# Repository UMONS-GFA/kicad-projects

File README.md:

# kicad-projects (NOT USED ANYMORE !)

## Configuring libraries in a project

Open your .sch file -> Preferences -> Component libraries  

Add component library files and choose your .lib files from the project_libs directory.  

## Configuring footprints in a project

* In project window, click new directory, rename it project_libs
* Add .lib files in this folder
* create project\_footprint.pretty sub-directory in project_libs
* Add kicad_mods in this sub-directory

Now in footprint editor, preferences -> footprint libraries manager-> project specific libraries click on on "Append Library"  

Example:  

Nickname: project  
Library path: ${KPRJMOD}/project\_libs/project\_footprints.pretty

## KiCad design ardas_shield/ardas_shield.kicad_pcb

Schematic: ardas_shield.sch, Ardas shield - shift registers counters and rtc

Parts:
BT1: Battery; BATTERY_KEYSTONE_12mm
D1, D2, D3: LED; LED-0805
IC1: DS1307; SOIC-8-N
JP1: Jumper_NO_Small; small_no_jumper
P1: CONN_10; Pin_Header_Straight_1x10
P2, P3: CONN_8; Pin_Header_Straight_1x08
P4: CONN_ICSP; Socket_Strip_Straight_2x03
P5: CONN_6; Pin_Header_Straight_1x06
P6: TTL_COMM; Pin_Header_Angled_1x03
P7, P8, P9, P10: CONN_01X03; Pin_Header_Angled_1x03
R1: 10k; R_0805
R2, R3: 150 Ohm; R_0805
R4: 160 Ohm; R_0805
RP1: R_4x4.7k; R_Array_Convex_4x0603
RP2, RP3, RP4, RP5: R_4x10k; R_Array_Convex_4x0603
U1: 74HC595; SOIC-16_7.5x10.3mm_Pitch1.27mm
U2, U4: 74HC165; SOIC-16_3.9x9.9mm_Pitch1.27mm
U3, U6: SN74LV8154; TSSOP-20_4.4x6.5mm_Pitch0.65mm
X1: CRYSTAL; XTAL_ABRACON_ABS07

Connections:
+5V: D1.2, D2.2, D3.2, IC1.8 (VCC), P2.5, P4.2, P7.1, P8.1, P9.1, P10.1, RP1.1, RP1.5 (R4), RP1.6 (R3), RP1.7 (R2), RP2.1, RP2.2, RP2.3, RP2.4, RP4.3, RP4.5 (R4), RP5.1, RP5.2, RP5.3, RP5.4, U1.16 (VCC), U2.16 (VCC), U3.20 (VCC), U4.16 (VCC), U6.20 (VCC)
A04: IC1.5 (SDA), P1.9, RP1.4
A05: IC1.6 (SCL), P1.10, RP1.3
CH1: P10.3, U3.1 (CLKA)
CH2: P9.3, U3.2 (CLKB)
CH3: P8.3, U6.1 (CLKA)
CH4: P7.3, U6.2 (CLKB)
D00: P3.1, P6.2
D01: P3.2, P6.1
D02: IC1.7 (SQW), P3.3, RP1.2
D03: P3.4, U1.11 (SRCLK)
D05: P3.6, U1.14 (SER)
D06: P3.7, U1.12 (RCLK)
D07: P3.8, U2.9 (Q7)
D08: P1.1, U2.1 (PL), U4.1 (PL)
D09: P1.2, RP4.1, RP4.2, U2.15 (CE), U4.15 (CE)
D14: P5.1, U3.7 (RCLK), U6.7 (RCLK)
D15: P5.2, U2.2 (CP), U4.2 (CP)
D16: P5.3, R3.2
D17: P5.4, R2.2
GND: BT1.2, IC1.4 (GND), JP1.1, P1.7, P2.6, P2.7, P4.6, P6.3, P7.2, P8.2, P9.2, P10.2, R1.1, R4.2, RP3.5 (R4), RP3.6 (R3), RP3.7 (R2), RP3.8 (R1), RP4.7 (R2), RP4.8 (R1), U1.8 (GND), U2.8 (GND), U3.10 (GND), U4.8 (GND), U6.10 (GND)
unnamed: BT1.1, IC1.3 (VBAT), JP1.2
unnamed: D1.1, R2.1
unnamed: D2.1, R3.1
unnamed: D3.1, R4.1
unnamed: IC1.1 (X1), X1.1
unnamed: IC1.2 (X2), X1.2
unnamed: R1.2, U1.13 (G)
unnamed: RP1.8 (R1), U1.10 (SRCLR)
unnamed: RP2.5 (R4), U1.15 (QA), U3.6 (GBU)
unnamed: RP2.6 (R3), U1.1 (QB), U3.5 (GBL)
unnamed: RP2.7 (R2), U1.2 (QC), U3.4 (GAU)
unnamed: RP2.8 (R1), U1.3 (QD), U3.3 (GAL)
unnamed: RP3.1, U3.8 (RCOA)
unnamed: RP3.2, U3.9 (CLKBEN)
unnamed: RP3.3, U6.8 (RCOA)
unnamed: RP3.4, U6.9 (CLKBEN)
unnamed: RP4.4, U6.11 (CCLR)
unnamed: RP4.6 (R3), U3.11 (CCLR)
unnamed: RP5.5 (R4), U1.4 (QE), U6.6 (GBU)
unnamed: RP5.6 (R3), U1.5 (QF), U6.5 (GBL)
unnamed: RP5.7 (R2), U1.6 (QG), U6.4 (GAU)
unnamed: RP5.8 (R1), U1.7 (QH), U6.3 (GAL)
unnamed: U2.3 (D4), U3.15 (Y4)
unnamed: U2.4 (D5), U3.14 (Y5)
unnamed: U2.5 (D6), U3.13 (Y6)
unnamed: U2.6 (D7), U3.12 (Y7)
unnamed: U2.10 (DS), U4.9 (Q7)
unnamed: U2.11 (D0), U3.19 (Y0)
unnamed: U2.12 (D1), U3.18 (Y1)
unnamed: U2.13 (D2), U3.17 (Y2)
unnamed: U2.14 (D3), U3.16 (Y3)
unnamed: U4.3 (D4), U6.15 (Y4)
unnamed: U4.4 (D5), U6.14 (Y5)
unnamed: U4.5 (D6), U6.13 (Y6)
unnamed: U4.6 (D7), U6.12 (Y7)
unnamed: U4.11 (D0), U6.19 (Y0)
unnamed: U4.12 (D1), U6.18 (Y1)
unnamed: U4.13 (D2), U6.17 (Y2)
unnamed: U4.14 (D3), U6.16 (Y3)

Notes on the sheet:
Arduino Uno R3 connectors
SHOULDN'T WE SET PIN 10 TO GND OR VCC?

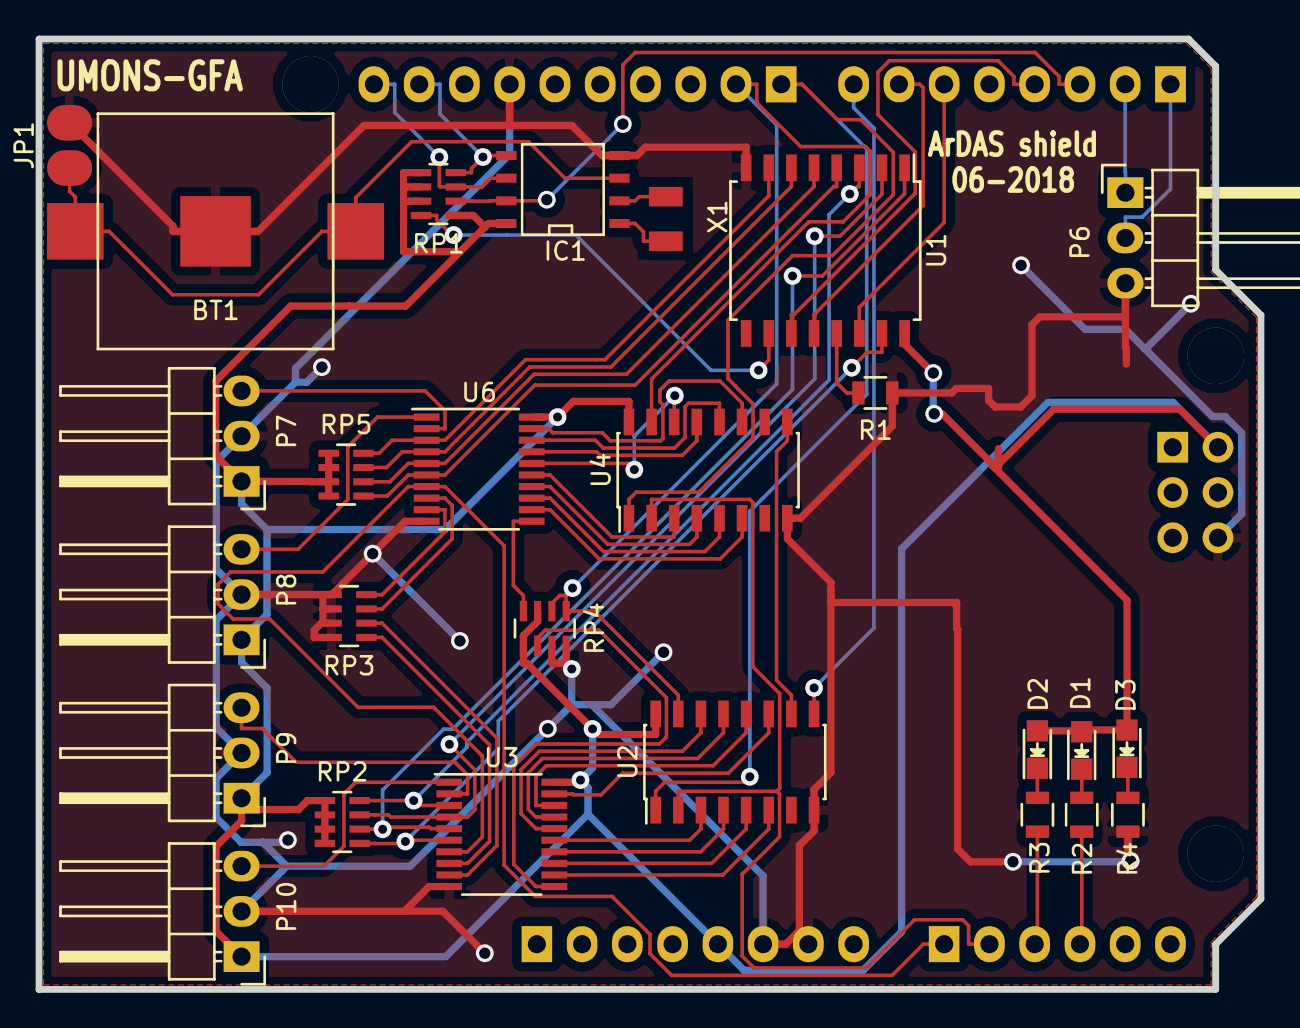
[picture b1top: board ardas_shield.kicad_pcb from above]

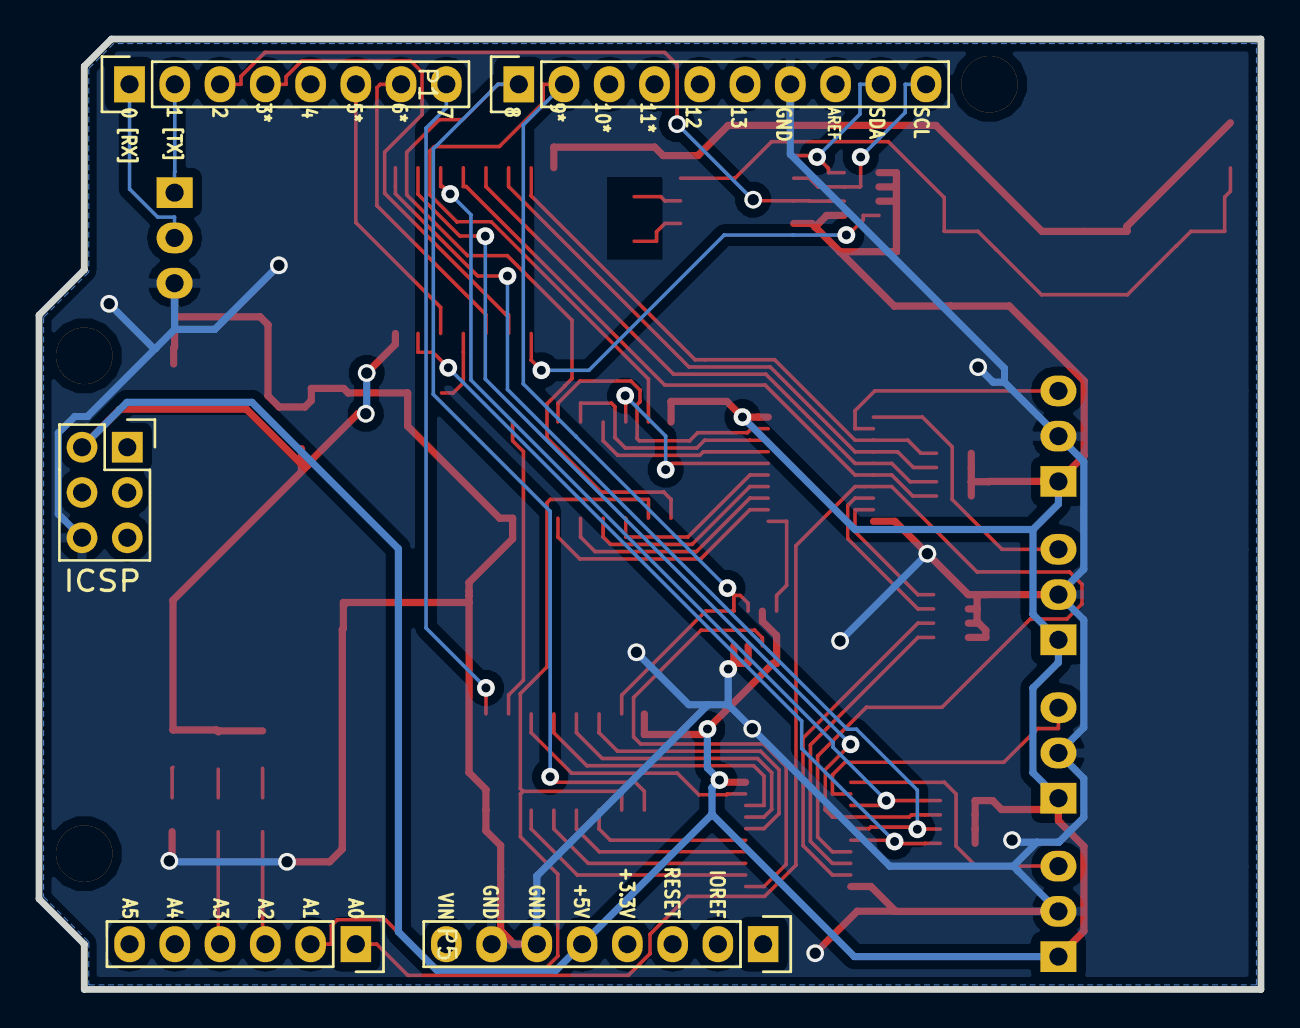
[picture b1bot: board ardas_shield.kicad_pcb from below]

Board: 2 copper layers, 68.6 x 53.3 mm, 34 parts (5 on the bottom side), 60 nets.

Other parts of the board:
V4, V5, V6: MountingHole_125mil

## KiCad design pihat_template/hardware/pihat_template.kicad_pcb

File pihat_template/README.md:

# Raspberry Pi Hat Template #

This project is a template for a Raspberry Pi Hat that was build on the guide lines published on github by the Raspberry Pi foundation. This template is designed to make it easier for hardware developers to design there own Rasberry Pi hats. The template was designed as a comprimse of cost, solderabilty, and footprint. The board has about 80% of its space still avalible to the user. The board also provides typical voltages that are required in many projects. The board is also capable of powering the Raspberry Pi. This makes this template sutable for development in automotive, industrial and home applications.

*This project is licensed under the CERN OHL v1.2*

### Features ###

- Input voltage 5.5v - 25v
- 5v supply from DC/DC @ 2.1A
- 3.3v supply from LDO @ 1.5A
- Backpowering protection ciruit
- Device ID eeprom
- Compliant with Raspberry Pi Hat specifications

### Basic Usage Guide ###

To use this template first you must clone the repository to some working directory. If you are in windows you can just download the zip right from git.  

```
git clone http://git.openfet.com/julien/pihat-template
```
Open the project in KiCad, you may need to add the library "project-libs" using the library wizard. Then you can add your own components, once the components are added you can tie them to the 3.3v or 5v net depending on what voltages are required. Once done you can then choose the components from CvPCB application. Export the netlist and then import it in PCBNew. 

### Customized design GFA-UMONS ###
2017/10/31 Changed LM3489 footprint from MSOP to VSSOP

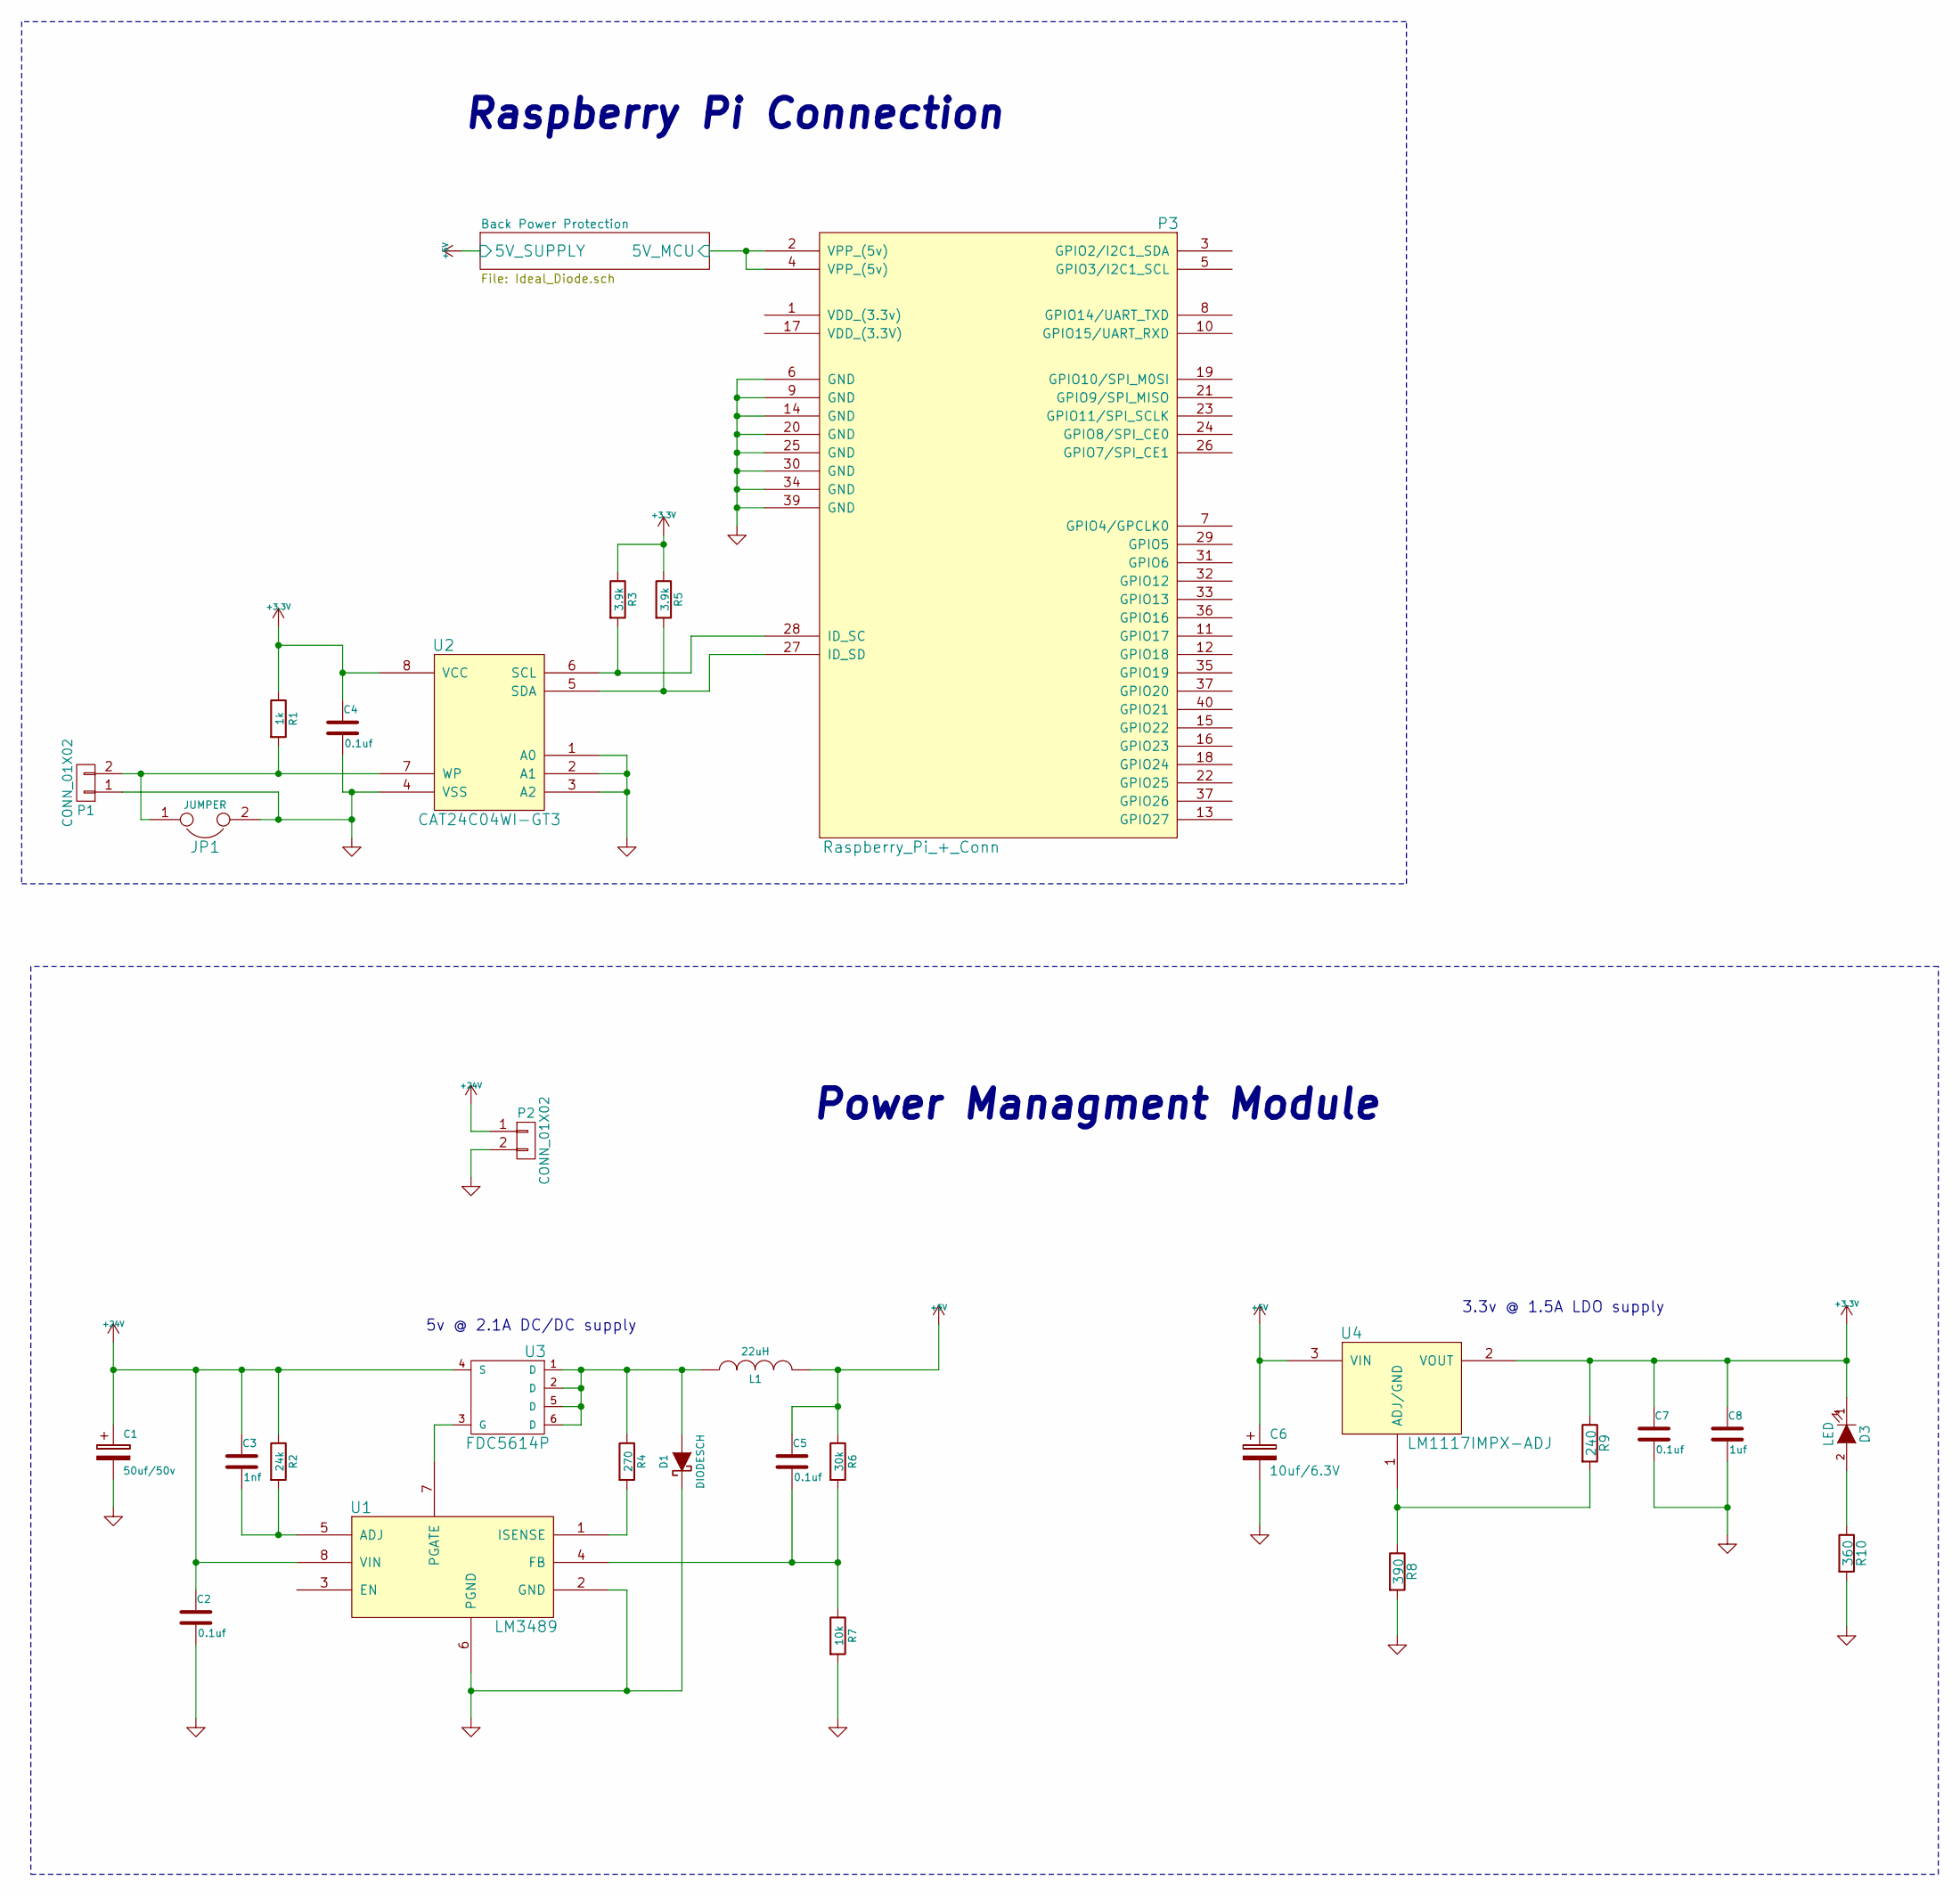
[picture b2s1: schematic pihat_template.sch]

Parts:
C1: 50uf/50v; c_elec_6.3x7.7; Mouser Part No. 647-UUR1H470MCL6GS
C2, C4, C5, C7: 0.1uf; c_0805; Mouser Part No. 810-C1005X5R1H104K
C3: 1nf; c_0805; Mouser Part No. 810-C1005C0G2A102J5C
C6: 10uf/6.3V; c_elec_4x5.3; Mouser Part No. 5985-AVS16V100-F
C8: 1uf; c_0805; Mouser Part No. 810-C1005X5R1H104K
D1: DIODESCH; do214aa; Farnell Part No. 2628293
D3: LED; Led_0603; Mouser Part No. 743-HT-191USD
JP1: JUMPER; r_0603; Farnell Part No. ?
L1: 22uH; inductor_smd_8x5mm; Mouser Part No. 652-SRN8040-220M
P1: CONN_01X02; pin_strip_2; Farnell Part No. ?
P2: CONN_01X02; mkds_1,5-2; Mouser Part No. 651-1904383
P3: Raspberry_Pi_+_Conn; pin_socket_20x2_mirrored; Mouser Part No. 517-30340-6002
R1: 1k; r_0805; Mouser Part No. 754-RR0510P-102D
R2: 24k; r_0805; Mouser Part No. 71-CRCW0402-24K-E3
R3, R5: 3.9k; r_0805; Mouser Part No. 71-CRCW04023K90FKED
R4: 270; r_0805; Mouser Part No. 667-ERJ-P6WJ271V
R6: 30k; r_0805; Mouser Part No. 594-MCT06030C3002FP5
R7: 10k; r_0805; Mouser Part No. 71-CRCW0603-10K-E3
R8: 390; r_0805; Mouser Part No. 594-MCT06030C3900FP5
R9: 240; r_0805; Mouser Part No. 754-RR0816P-241D
R10: 360; r_0805; Mouser Part No. 71-CRCW0603316RFKEB
U1: LM3489; VSSOP-8_3.0x3.0mm_Pitch0.65mm; Farnell Part No. 1312570
U2: CAT24C04WI-GT3; Farnell Part No. 2463704
U3: FDC5614P; Mouser Part No. 512-FDC5614P
U4: LM1117IMPX-ADJ; sot223; Mouser Part No. 926-M1117IMPXADJNOPB

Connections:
+3V3: C4.1, C7.1, C8.1, D3.1 (K), R1.1, R3.1, R5.1, R9.1, U2.8 (VCC), U4.2 (VOUT)
+5V: C5.1, C6.1, L1.2, R6.1, U4.3 (VIN); also elsewhere on the board
+24V: C1.1, C2.1, C3.1, P2.1, R2.1, U1.8 (VIN), U3.4 (S)
/Back Power Protection/5V_MCU: P3.2 (VPP_(5v)), P3.4 (VPP_(5v)); also elsewhere on the board
GND: C1.2, C2.2, C4.2, C6.2, C7.2, C8.2, D1.1 (K), JP1.2, P1.1, P2.2, P3.6 (GND), P3.9 (GND), P3.14 (GND), P3.20 (GND), P3.25 (GND), P3.30 (GND), P3.34 (GND), P3.39 (GND), R7.2, R8.2, R10.2, U1.2 (GND), U1.6 (PGND), U2.1 (A0), U2.2 (A1), U2.3 (A2), U2.4 (VSS); also elsewhere on the board
unnamed: C3.2, R2.2, U1.5 (ADJ)
unnamed: C5.2, R6.2, R7.1, U1.4 (FB)
unnamed: D1.2 (A), L1.1, R4.1, U3.1 (D), U3.2 (D), U3.5 (D), U3.6 (D)
unnamed: D3.2 (A), R10.1
unnamed: JP1.1, P1.2, R1.2, U2.7 (WP)
unnamed: P3.27 (ID_SD), R5.2, U2.5 (SDA)
unnamed: P3.28 (ID_SC), R3.2, U2.6 (SCL)
unnamed: R4.2, U1.1 (ISENSE)
unnamed: R8.1, R9.2, U4.1 (ADJ/GND)
unnamed: U1.7 (PGATE), U3.3 (G)

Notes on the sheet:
Raspberry Pi Connection
Power Managment Module
5v @ 2.1A DC/DC supply
3.3v @ 1.5A LDO supply

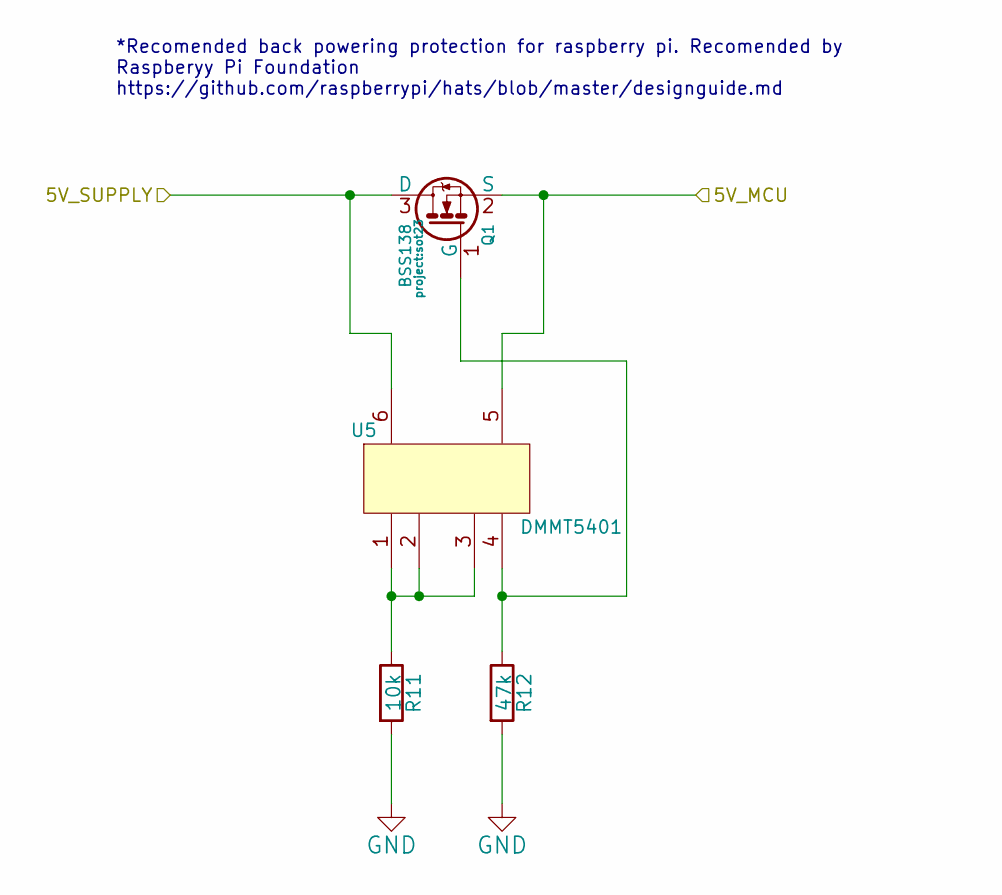
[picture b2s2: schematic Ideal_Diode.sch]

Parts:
Q1: BSS138; sot23; Mouser Part No. 621-DMG2305UX-13
R11: 10k; r_0805; Mouser Part No. 71-CRCW0402-10K-E3
R12: 47k; r_0805; Mouser Part No. 667-ERJ-2RKF4702X
U5: DMMT5401; sot23-6; Mouser Part No. 621-DMMT5401-7-F

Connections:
+5V: Q1.3 (D), U5.6; also elsewhere on the board
/Back Power Protection/5V_MCU: Q1.2 (S), U5.5; also elsewhere on the board
GND: R11.2, R12.2; also elsewhere on the board
unnamed: Q1.1 (G), R12.1, U5.4
unnamed: R11.1, U5.1, U5.2, U5.3

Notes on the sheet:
*Recomended back powering protection for raspberry pi. Recomended by Raspberyy Pi Foundation https://github.com/raspberrypi/hats/blob/master/designguide.md

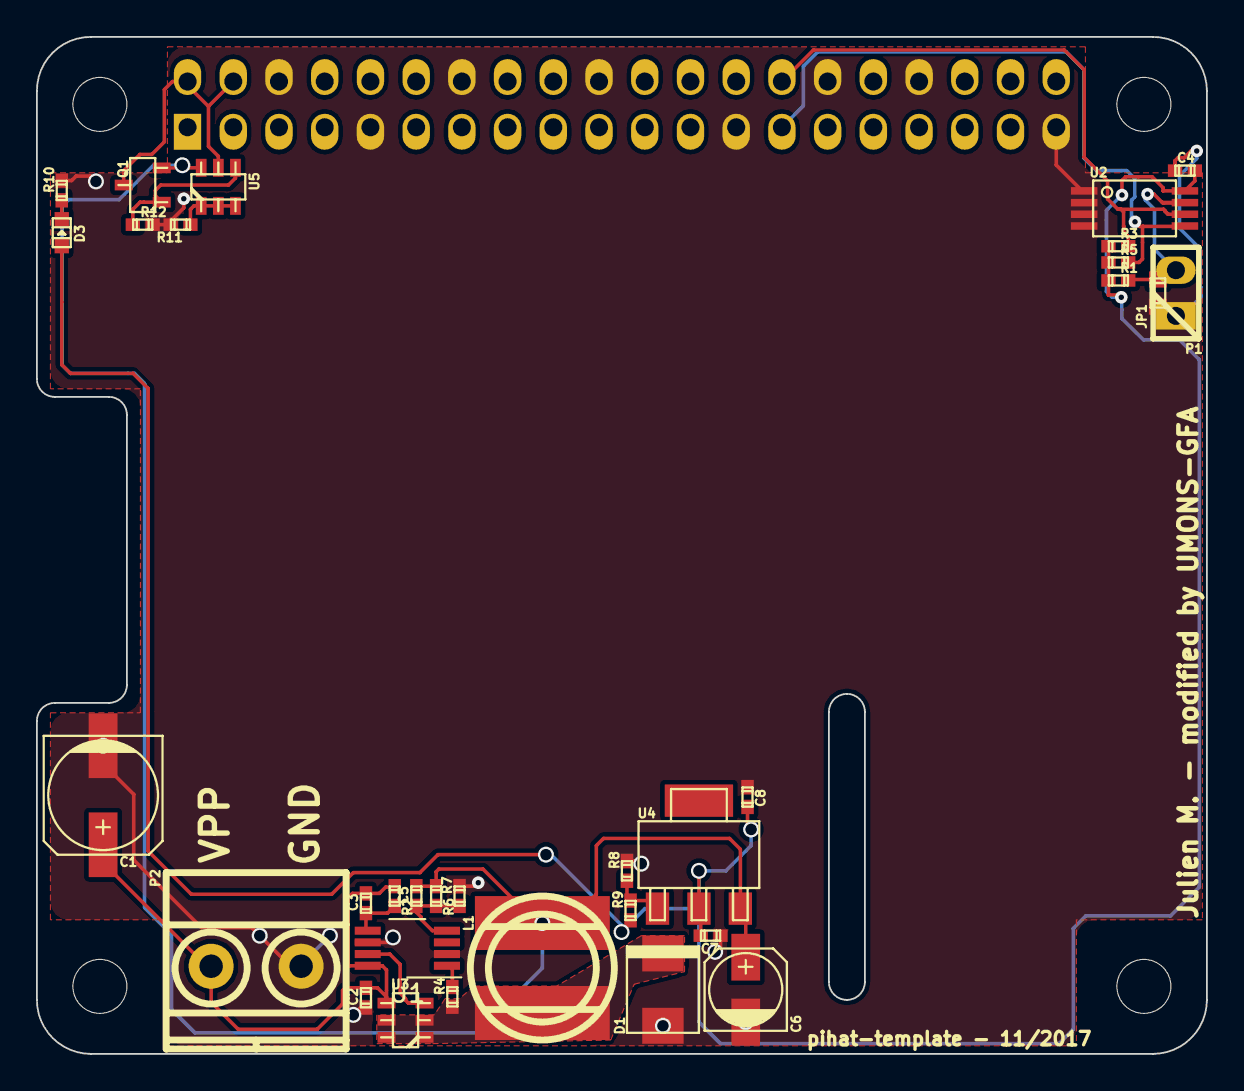
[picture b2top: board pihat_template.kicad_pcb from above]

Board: 2 copper layers, 65.0 x 56.5 mm, 33 parts (1 on the bottom side), 17 nets.

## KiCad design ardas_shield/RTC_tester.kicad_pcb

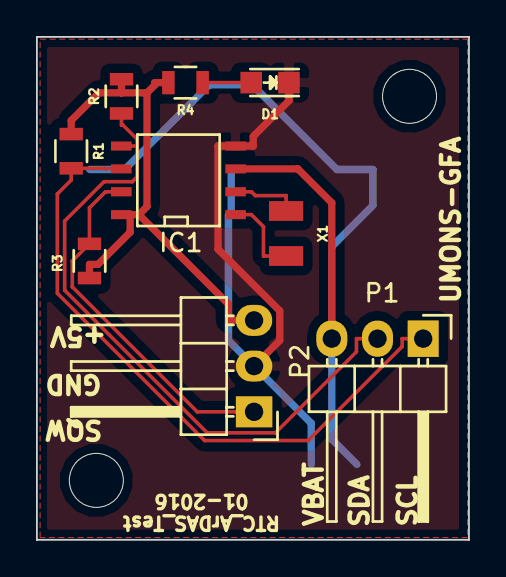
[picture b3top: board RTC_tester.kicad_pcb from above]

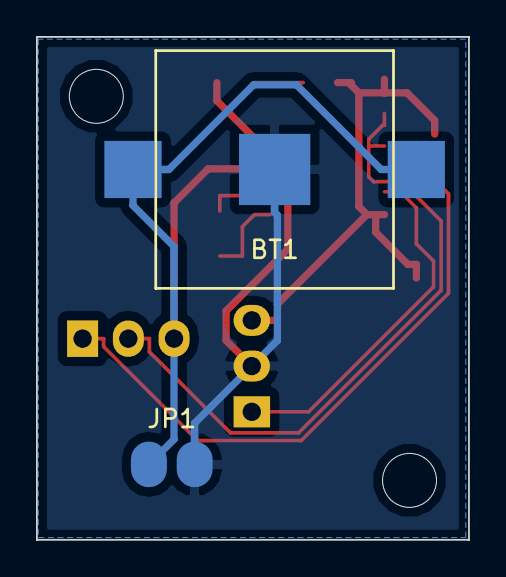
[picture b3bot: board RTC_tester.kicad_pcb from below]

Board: 2 copper layers, 24.0 x 27.9 mm, 13 parts (2 on the bottom side), 9 nets.

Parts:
BT1: Battery; BATTERY_KEYSTONE_12mm
D1: Led_Small; LED-0805
IC1: DS1307; SOIC-8-N
JP1: Jumper_NO_Small; small_no_jumper
MH2, MH3: MountingHole_3mm
P1: I2C/SQW; Pin_Header_Angled_1x03
P2: PWR; Pin_Header_Angled_1x03
R1, R2: 4.7K; R_0805
R3: 10K; R_0805
R4: 150; R_0805
X1: CRYSTAL; XTAL_ABRACON_ABS07

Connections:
+5V: IC1.8, P2.3, R1.1, R2.1, R3.1, R4.1
GND: BT1.2, D1.1, IC1.4, JP1.1, P2.2
unnamed: D1.2, R4.2
unnamed: IC1.1, X1.1
unnamed: IC1.2, X1.2
SCL: IC1.6, P1.1, R1.2
SDA: IC1.5, P1.2, R2.2
SQW: IC1.7, P2.1, R3.2
VBAT: BT1.1, IC1.3, JP1.2, P1.3

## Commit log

2016-01-13 add initial files for ArDAS shield
2016-01-13 add more components
2016-01-13 rename Ardas
2016-01-13 Updated ardas_shield geometry and microSD. Rerouted shield
2016-01-15 updated to v0.49
2016-01-15 add datasheet links
2016-01-19 changed resitances arrays footprints
2016-01-21 upgraded Ardas shield + RTC_tester
2016-01-21 corrected v-scoring issue
2016-01-25 add details for BOM
2016-01-25 add BOM
2016-02-08 updated ardas_shield+RTC_tester.kicad_pcb
2016-02-08 ardas shield
2016-02-11 modified RGB LED and SD-Card pinout and buffer VCC
2016-02-11 updated SD card and RGB-LED
2017-09-29 added pihat_template
2017-10-31 changed LM3489 footprint
2017-10-31 add VSSOP as a project footprint
2017-10-31 add link to libraries
2017-10-31 add doc
2017-10-31 update components
2017-10-31 change from cache libs to project_libs libs
2017-10-31 added farnell part no.
2017-11-02 added silk UMONS-GFA + name
2017-11-06 pihat 1-wire first commit
2017-11-06 updated vias for EuroCircuits standards
2017-11-06 remove wrong release
2017-11-06 add gigalib libraries
2017-11-06 added and links to 3D models for modules in project lib
2017-11-06 raspberry pi connector moved to back side of board
2017-11-07 fixed broken path to mkds_1,5-2 3D module
2017-11-07 add missing component
2017-11-16 refactor larger components
2017-11-16 refactor large components
2017-11-16 Refactored PCB with larger components
2017-11-16 add gitignore
2018-05-22 remove bak files
2018-05-22 remove sd card components
2018-05-22 add new leds and footprints
2018-05-23 replace 4 resistors groups with separated resistor 0805
2018-05-23 remove old junctions
2018-05-25 complete componenents metadatas with Kifield
2018-05-25 update pcbnew layout
2018-05-30 ardas_shield.rules
2018-05-30 removing CON1 SD card
2018-05-30 removing 5V-3.3V converter components from scheme
2018-05-30 removing JP2 from scheme
2018-05-30 resolve rules check problems
2018-05-30 resolve power input problem on U1
2018-05-30 remove sdcard an 5V-3V from PCB
2018-05-30 remove sd card protected area
2018-05-30 replace RGB Led circuit by separated leds
2018-05-30 add footprints for new leds and resistors
2018-05-30 add values for resistors
2018-05-30 add new leds and resistors to the PCB
2018-05-30 update scheme metadatas

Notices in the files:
pihat_template/hardware/pihat_template.kicad_pcb:
License: CERN OHL V1.2
